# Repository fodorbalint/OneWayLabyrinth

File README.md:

# The one-way labyrinth algorithm

This research aims to solve the following problem:<br />
"Draw a line that goes through an n x n grid (where n is an odd number), passing through each field once. The line has to start from the field at the upper left corner (1,1) and end at (n,n). At any time it is allowed to move left, right, up or down, and it has to randomly choose between the available fields."

At first sight it may look easy. But look at the following example:

<!---->

Based on the black line's movement, blue fragments were drawn to indicate a path we have to go through in the future in order to fill the board.<br />
Do you see why the situation is impossible from now on?

The question is, is there a single rule or a set of rules that will guarantee you can draw a labyrinth of any size? Or do the rules get infinitely complex?

To assist with the research, I have written a computer program. In the beginning, I let it run on a 21 x 21 field, and whenever I noticed a trouble, I coded the solution into it. While you can discover many patterns this way, they will be random and do not help in gaining a fundemental understanding. At one point you will find things get too complex, and you are still far from solving the 21 x 21 board.<br />
That's where a gradual approach comes in.

Due to the length of the study, it cannot be displayed on this one page. To continue reading, download the PDF files for <a href="A5 web.pdf"/>screen reading</a> or <a href="A5 print.pdf"/>to be printed out.</a>)

---

The project contains the source code for use with Visual Studio. To start the program, run OneWayLabyrinth.exe in the folder "bin/Debug/net6.0-windows".

Screenshots:

<br />
<br />

---

Hotkeys:

Enter: Reload or Close error message<br />
Ctrl + S: Save path<br />
Right arrow: Step forward<br />
Left arrow: Step back<br />
Ctrl/Shift + arrows: step in direction if possible. If CapsLock is on, pressing the Ctrl or Shift keys is not necessary.<br />
Space: Run automatically / Stop automatic running

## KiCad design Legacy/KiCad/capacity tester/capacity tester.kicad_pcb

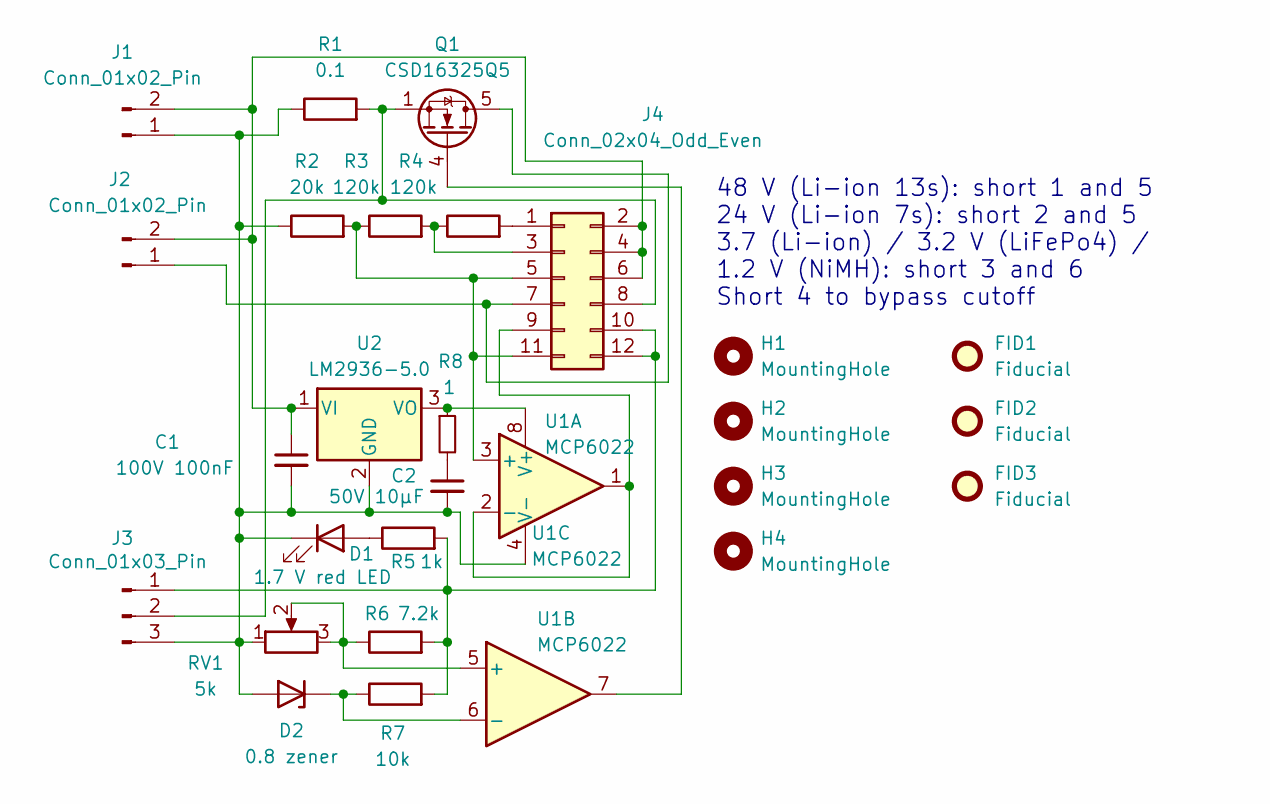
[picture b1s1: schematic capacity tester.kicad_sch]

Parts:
C1: 100V 100nF; C_0805_2012Metric_Pad1.18x1.45mm_HandSolder
C2: 50V 10µF; C_1206_3216Metric_Pad1.33x1.80mm_HandSolder
D1: 1.7 V red LED; LED_D5.0mm
D2: 0.8 zener; D_DO-35_SOD27_P7.62mm_Horizontal
FID1, FID2, FID3: Fiducial; Fiducial_1mm_Mask3mm
H1, H2, H3, H4: MountingHole; MountingHole_3.2mm_M3
J1: Conn_01x02_Pin; AMASS_XT30U-M_1x02_P5.0mm_Vertical
J2: Conn_01x02_Pin; AMASS_XT30U-F_1x02_P5.0mm_Vertical
J3: Conn_01x03_Pin; KF2510_1x03_P2.54mm_Vertical
J4: Conn_02x04_Odd_Even; PinHeader_2x06_P2.54mm_Vertical
Q1: CSD16325Q5; Infineon_PG-TDSON-8_6.15x5.15mm
R1: 0.1; Constantan_R_1.2x20
R2: 20k; R_Axial_DIN0207_L6.3mm_D2.5mm_P10.16mm_Horizontal
R3, R4: 120k; R_Axial_DIN0207_L6.3mm_D2.5mm_P10.16mm_Horizontal
R5: 1k; R_Axial_DIN0207_L6.3mm_D2.5mm_P10.16mm_Horizontal
R6: 7.2k; R_Axial_DIN0207_L6.3mm_D2.5mm_P10.16mm_Horizontal
R7: 10k; R_Axial_DIN0207_L6.3mm_D2.5mm_P10.16mm_Horizontal
R8: 1; R_1206_3216Metric_Pad1.30x1.75mm_HandSolder
RV1: 5k; Potentiometer_Bourns_3386W_Horizontal
U1: MCP6022; SOIC-8_3.9x4.9mm_P1.27mm_down_handsolder
U2: LM2936-5.0; SOIC-8_3.9x4.9mm_P1.27mm_down_ldo_handsolder

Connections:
unnamed: C2.1, R8.2
unnamed: D1.2 (A), R5.1
unnamed: C1.2, C2.2, D1.1 (K), D2.2 (A), J1.1, J3.3, R1.1, R2.1, RV1.1, U1.4 (V-), U2.2 (GND)
unnamed: D2.1 (K), R7.1, U1.6 (-)
unnamed: C1.1, J1.2, J2.2, J4.2, J4.4, J4.6, U2.1 (VI)
unnamed: J2.1, J4.7, Q1.5 (D)
unnamed: J3.1, J4.10, J4.12, R5.2, R6.2, R7.2
unnamed: J3.2, J4.8, Q1.1 (S), Q1.2 (S), Q1.3 (S), R1.2
unnamed: J4.1, R4.2
unnamed: J4.3, R3.2, R4.1
unnamed: J4.9, U1.1, U1.2 (-)
unnamed: J4.5, J4.11, R2.2, R3.1, U1.3 (+)
unnamed: Q1.4 (G), U1.7
unnamed: R6.1, RV1.2, RV1.3, U1.5 (+)
unnamed: R8.1, U1.8 (V+), U2.3 (VO)

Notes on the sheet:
48 V (Li-ion 13s): short 1 and 5 24 V (Li-ion 7s): short 2 and 5 3.7 (Li-ion) / 3.2 V (LiFePo4) / 1.2 V (NiMH): short 3 and 6 Short 4 to bypass cutoff

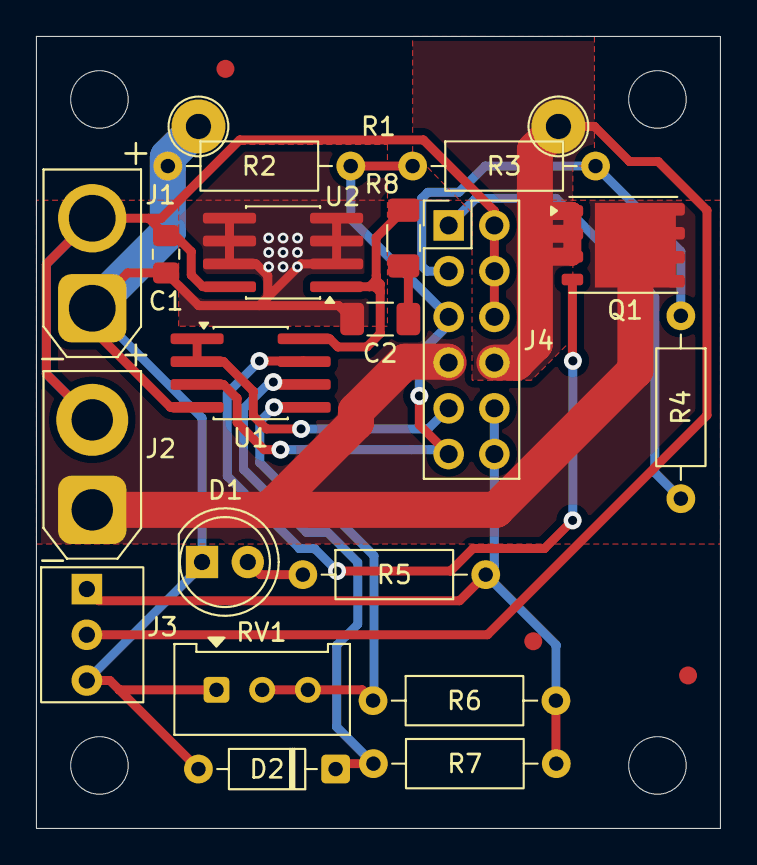
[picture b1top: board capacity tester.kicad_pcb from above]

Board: 2 copper layers, 38.0 x 44.0 mm, 27 parts (0 on the bottom side), 15 nets.

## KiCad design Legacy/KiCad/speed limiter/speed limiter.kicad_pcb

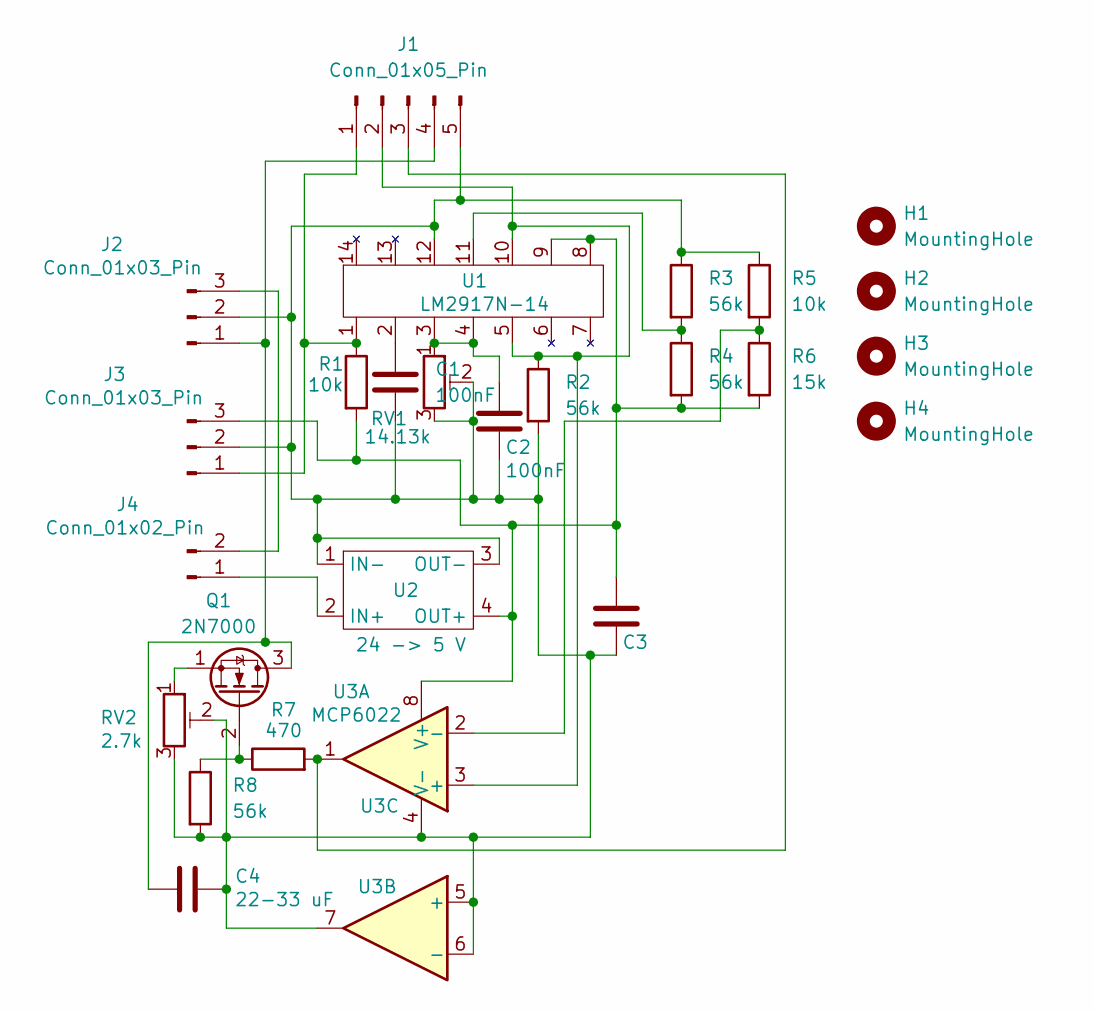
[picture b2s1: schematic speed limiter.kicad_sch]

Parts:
C1, C2: 100nF; C_Rect_L7.0mm_W2.0mm_P5.00mm
C3: C_Rect_L7.0mm_W2.0mm_P5.00mm
C4: 22-33 uF; C_Rect_L7.0mm_W2.0mm_P5.00mm
H1, H2, H3, H4: MountingHole; MountingHole_3.2mm_M3
J1: Conn_01x05_Pin; JST_XH_B5B-XH-A_1x05_P2.50mm_Vertical
J2, J3: Conn_01x03_Pin; JST_XH_B3B-XH-A_1x03_P2.50mm_Vertical
J4: Conn_01x02_Pin; JST_XH_B2B-XH-A_1x02_P2.50mm_Vertical
Q1: 2N7000; TO-92_HandSolder
R1, R5: 10k; R_Axial_DIN0207_L6.3mm_D2.5mm_P10.16mm_Horizontal
R2, R3, R4, R8: 56k; R_Axial_DIN0207_L6.3mm_D2.5mm_P10.16mm_Horizontal
R6: 15k; R_Axial_DIN0207_L6.3mm_D2.5mm_P10.16mm_Horizontal
R7: 470; R_Axial_DIN0207_L6.3mm_D2.5mm_P10.16mm_Horizontal
RV1: 14.13k; Potentiometer_Bourns_3386W_Horizontal
RV2: 2.7k; Potentiometer_Bourns_3386W_Horizontal
U1: LM2917N-14; DIP-14_W7.62mm_LongPads
U2: 24 -> 5 V; Buck_converter
U3: MCP6022; DIP-8_W7.62mm_LongPads

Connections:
unnamed: C1.1, U1.2
unnamed: C2.1, RV1.1, U1.3, U1.4
unnamed: J1.1, J3.1, R1.1, U1.1
unnamed: J1.2, R2.1, U1.5, U1.10, U3.3 (+)
unnamed: J1.3, R7.2, U3.1
unnamed: C4.1, J1.4, J2.1, Q1.3 (D)
unnamed: C1.2, C2.2, C3.2, C4.2, J1.5, J2.2, J3.2, R2.2, R3.1, R5.1, R8.2, RV1.2, RV1.3, RV2.2, RV2.3, U1.12, U2.1 (IN-), U2.3 (OUT-), U3.4 (V-), U3.5 (+), U3.6 (-), U3.7
unnamed: J2.3, J4.2
unnamed: C3.1, J3.3, R1.2, R4.2, R6.2, U1.8, U1.9, U2.4 (OUT+), U3.8 (V+)
unnamed: J4.1, U2.2 (IN+)
unnamed: Q1.2 (G), R7.1, R8.1
unnamed: Q1.1 (S), RV2.1
unnamed: R3.2, R4.1, U1.11
unnamed: R5.2, R6.1, U3.2 (-)

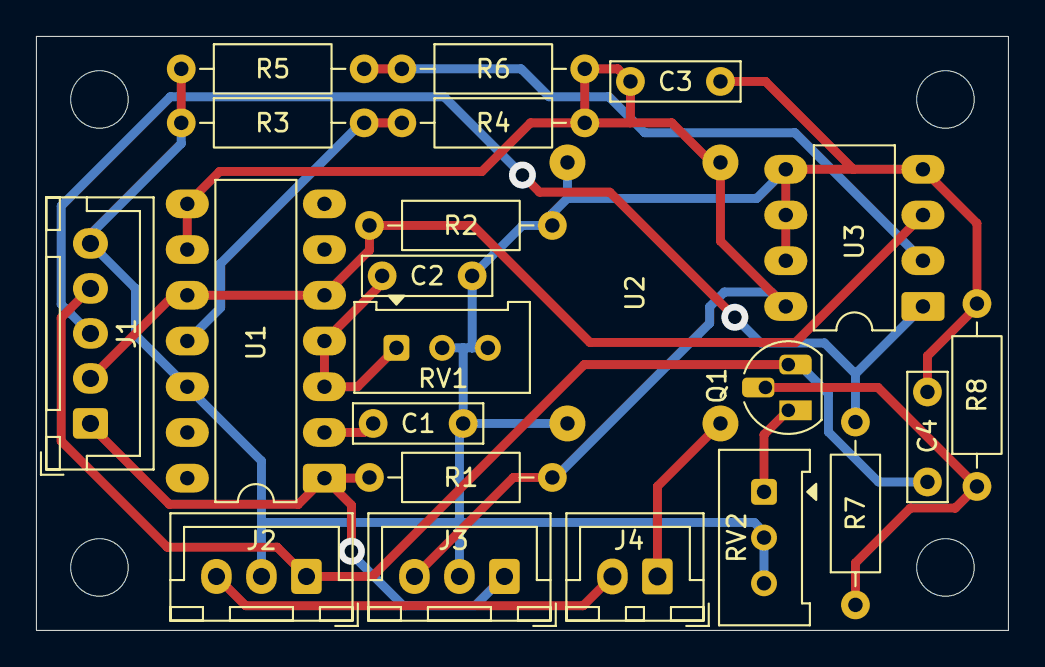
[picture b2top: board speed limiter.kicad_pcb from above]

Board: 2 copper layers, 54.0 x 33.0 mm, 26 parts (0 on the bottom side), 14 nets.

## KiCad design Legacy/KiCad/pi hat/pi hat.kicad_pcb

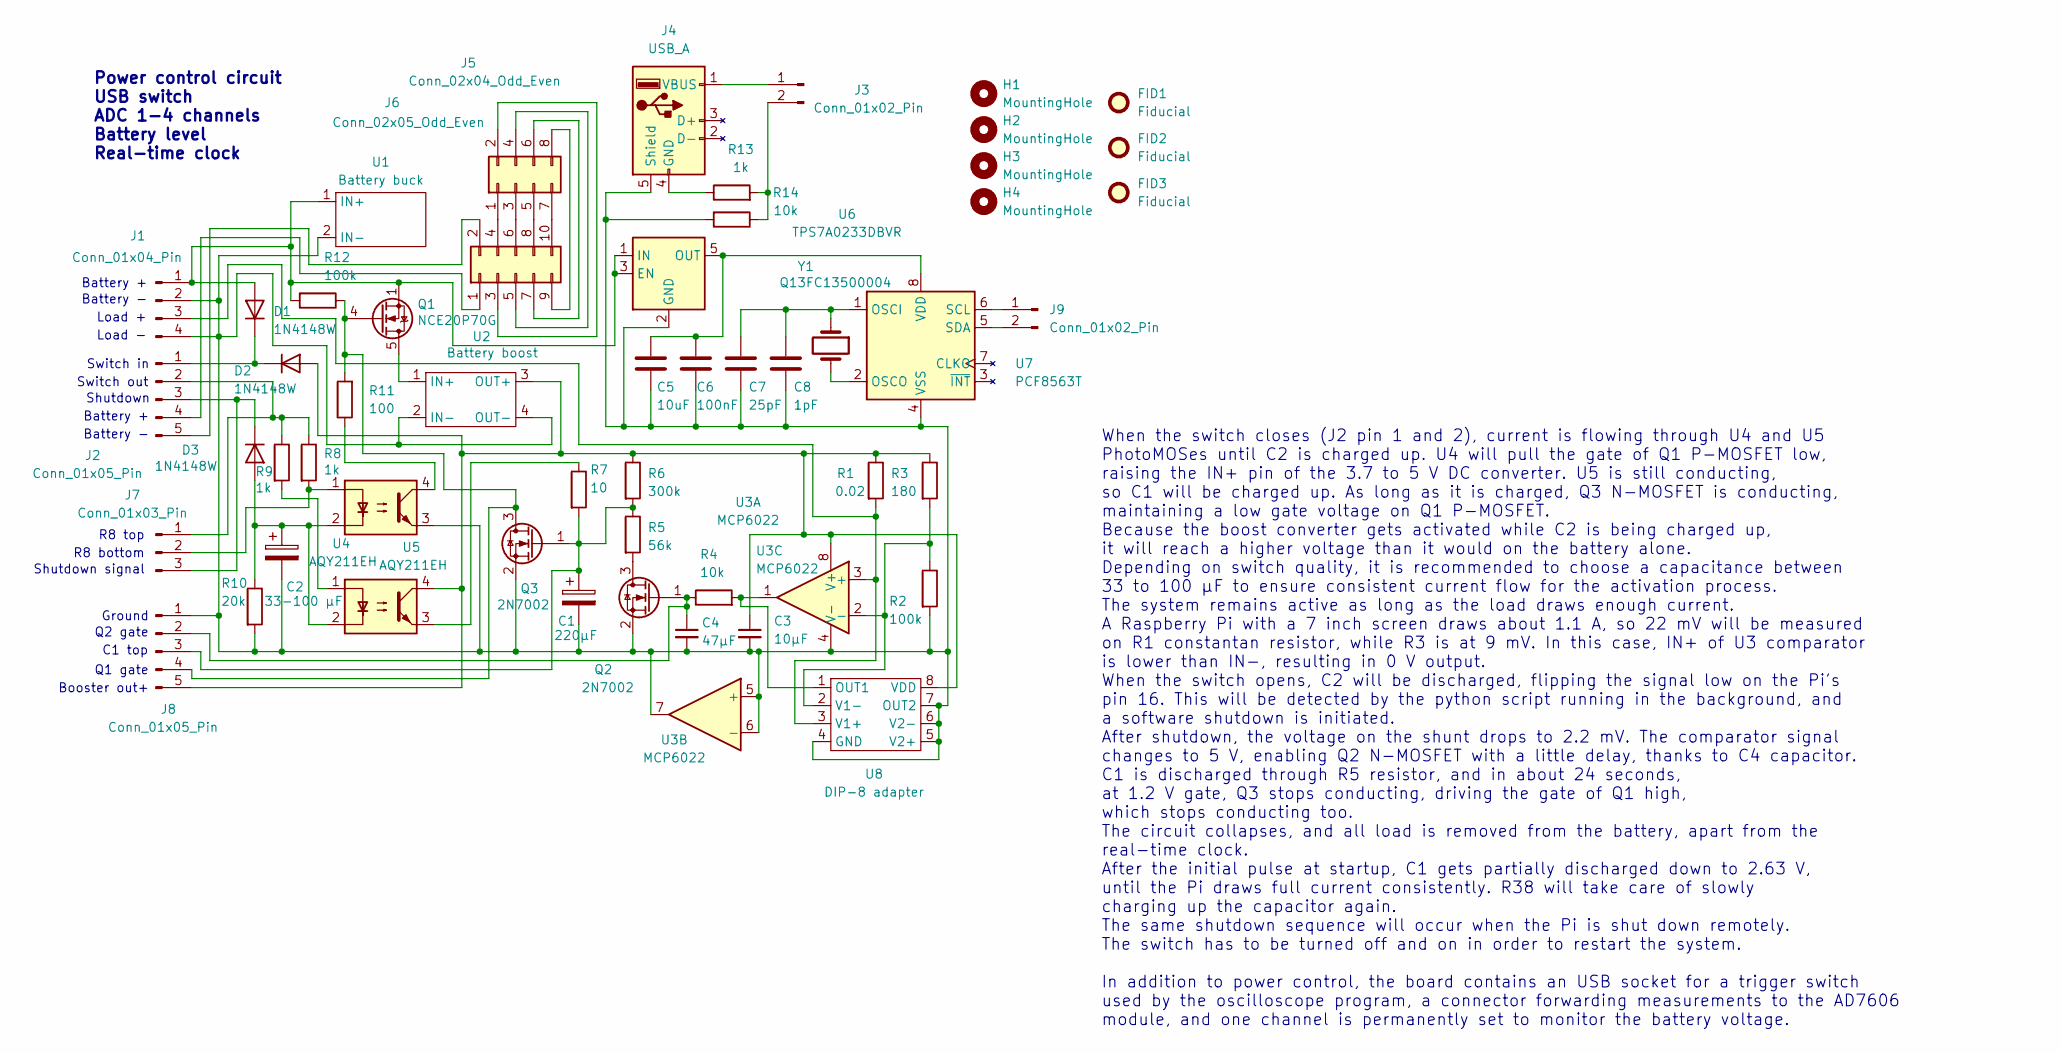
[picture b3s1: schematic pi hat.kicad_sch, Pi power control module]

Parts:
C1: 220µF; CP_Radial_D6.3mm_P2.50mm
C2: 33-100 µF; CP_Radial_D5.0mm_P2.00mm
C3: 10µF; C_1206_3216Metric_Pad1.33x1.80mm_HandSolder
C4: 47µF; C_1206_3216Metric_Pad1.33x1.80mm_HandSolder
C5: 10uF; C_1206_3216Metric_Pad1.33x1.80mm_HandSolder
C6: 100nF; C_1206_3216Metric_Pad1.33x1.80mm_HandSolder
C7: 25pF; C_1206_3216Metric_Pad1.33x1.80mm_HandSolder
C8: 1pF; C_1206_3216Metric_Pad1.33x1.80mm_HandSolder
D1, D2, D3: 1N4148W; D_SOD-123F
FID1, FID2, FID3: Fiducial; Fiducial_1mm_Mask3mm
H1, H2, H3, H4: MountingHole; MountingHole_3.2mm_M3
J1: Conn_01x04_Pin; KF2510_1x04_P2.54mm_Vertical
J2, J8: Conn_01x05_Pin; KF2510_1x05_P2.54mm_Vertical
J3, J9: Conn_01x02_Pin; KF2510_1x02_P2.54mm_Vertical
J4: USB_A; USB_A_Receptacle_Custom
J5: Conn_02x04_Odd_Even; PinHeader_2x04_P2.54mm_Horizontal
J6: Conn_02x05_Odd_Even; PinHeader_2x05_P2.54mm_Vertical
J7: Conn_01x03_Pin; KF2510_1x03_P2.54mm_Vertical
Q1: NCE20P70G; Infineon_PG-TDSON-8_6.15x5.15mm
Q2, Q3: 2N7002; SOT-23_Handsoldering_right
R1: 0.02; Constantan_R_1.2x10
R2, R12: 100k; R_1206_3216Metric_Pad1.30x1.75mm_HandSolder
R3: 180; R_1206_3216Metric_Pad1.30x1.75mm_HandSolder
R4, R14: 10k; R_1206_3216Metric_Pad1.30x1.75mm_HandSolder
R5: 56k; R_0805_2012Metric_Pad1.20x1.40mm_HandSolder
R6: 300k; R_0805_2012Metric_Pad1.20x1.40mm_HandSolder
R7: 10; R_1206_3216Metric_Pad1.30x1.75mm_HandSolder
R8, R9, R13: 1k; R_1206_3216Metric_Pad1.30x1.75mm_HandSolder
R10: 20k; R_0805_2012Metric_Pad1.20x1.40mm_HandSolder
R11: 100; R_1206_3216Metric_Pad1.30x1.75mm_HandSolder
U1: Battery buck; Battery_buck
U2: Battery boost; Battery_boost
U3: MCP6022; SOIC-8_3.9x4.9mm_P1.27mm_down_handsolder
U4, U5: AQY211EH; SOP-4_6.4x4.78mm_P2.54mm
U6: TPS7A0233DBVR; SOT-23-5_HandSoldering_down
U7: PCF8563T; SOIC-8_3.9x4.9mm_P1.27mm_down
U8: DIP-8 adapter; DIP-8_W7.62mm
Y1: Q13FC13500004; Crystal_SMD_3215-2Pin_3.2x1.5mm

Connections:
unnamed: D1.2 (A), J1.1, Q1.1 (S), Q1.2 (S), Q1.3 (S), R12.2, U1.1 (IN+), U6.1 (IN), U6.3 (EN)
unnamed: D1.1 (K), D2.1 (K), J2.1
unnamed: C3.1, D2.2 (A), J8.5, R1.1, R3.1, R6.1, U2.3 (OUT+), U3.8 (V+), U5.4, U8.8 (VDD)
unnamed: C2.1, D3.2 (A), R10.1, U4.2, U5.2
unnamed: D3.1 (K), J2.3, J7.3
unnamed: C1.2, C2.2, C3.2, C4.2, C5.2, C6.2, C7.2, C8.2, J1.2, J1.4, J4.5 (Shield), J8.1, Q2.2 (S), Q3.2 (S), R2.2, R10.2, R14.2, U1.2 (IN-), U2.2 (IN-), U2.4 (OUT-), U3.4 (V-), U3.5 (+), U3.6 (-), U3.7, U4.3, U6.2 (GND), U7.4 (VSS), U8.4 (GND), U8.5 (V2+), U8.6 (V2-), U8.7 (OUT2)
unnamed: J1.3, R1.2, U3.3 (+), U8.3 (V1+)
unnamed: J2.2, J7.1, R8.1, R9.1
unnamed: J2.4, J6.1
unnamed: J2.5, J6.2
unnamed: J3.1, J4.1 (VBUS)
unnamed: J3.2, R13.2, R14.1
unnamed: J4.4 (GND), R13.1
unnamed: J5.1, J6.4
unnamed: J5.2, J6.3
unnamed: J5.3, J6.6
unnamed: J5.4, J6.5
unnamed: J5.5, J6.8
unnamed: J5.6, J6.7
unnamed: J5.7, J6.10
unnamed: J5.8, J6.9
unnamed: J7.2, R8.2, U4.1
unnamed: C4.1, J8.2, Q2.1 (G), R4.1
unnamed: C1.1, J8.3, Q3.1 (G), R5.1, R6.2, R7.2
unnamed: J8.4, Q1.4 (G), Q3.3 (D), R11.2, R12.1
unnamed: J9.1, U7.6 (SCL)
unnamed: J9.2, U7.5 (SDA)
unnamed: Q1.5 (D), U2.1 (IN+)
unnamed: Q2.3 (D), R5.2
unnamed: R7.1, U5.3
unnamed: R9.2, U5.1
unnamed: R11.1, U4.4
unnamed: R2.1, R3.2, U3.2 (-), U8.2 (V1-)
unnamed: C5.1, C6.1, U6.5 (OUT), U7.8 (VDD)
unnamed: C7.1, C8.1, U7.1 (OSCI), Y1.1
unnamed: U7.2 (OSCO), Y1.2
unnamed: R4.2, U3.1, U8.1 (OUT1)

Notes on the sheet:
Ground
C1 top
Load -
R8 bottom
Q1 gate
Load +
Battery +
When the switch closes (J2 pin 1 and 2), current is flowing through U4 and U5 PhotoMOSes until C2 is charged up. U4 will pull the gate of Q1 P-MOSFET low, raising the IN+ pin of the 3.7 to 5 V DC converter. U5 is still conducting, so C1 will be charged up. As long as it is charged, Q3 N-MOSFET is c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
Booster out+
Shutdown
Battery -
Switch in
Power control circuit USB switch ADC 1-4 channels Battery level Real-time clock
R8 top
Switch out
Shutdown signal
Q2 gate

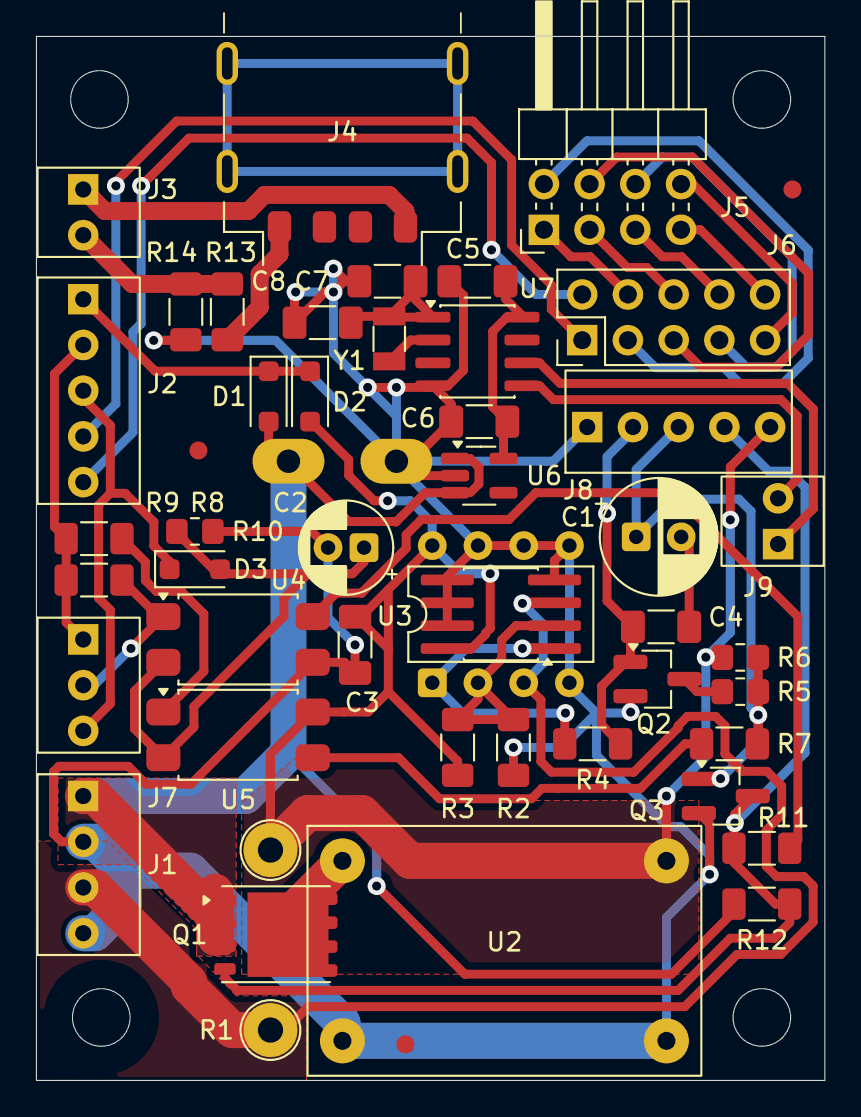
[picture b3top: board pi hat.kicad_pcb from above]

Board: 2 copper layers, 43.8 x 58.0 mm, 53 parts (1 on the bottom side), 37 nets.

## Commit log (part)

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2025-05-17 Remove obj folder from repository
2025-05-17 upload
2026-04-23 references renamed
2026-06-24 added legacy
